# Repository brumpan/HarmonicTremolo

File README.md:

# HarmonicTremolo
A harmonic tremolo effect board for audio

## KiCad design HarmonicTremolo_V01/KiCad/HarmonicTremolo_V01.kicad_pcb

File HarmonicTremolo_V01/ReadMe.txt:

// This project may be replicated by hobbiest and DIY enthusiasts only. The schematics, circuit, and PCB files are not to be used for profit by any commercial, private or third-party entity. \\

Author: Brendan Dickerson
Date: May 2022
Revision: 01
Title: Harmonic Tremolo
Description: Frequency dependent tremolo effect for audio.

This is an audio effect board that can easily be placed into any enclosure or compounded into an existing effects enclosure.

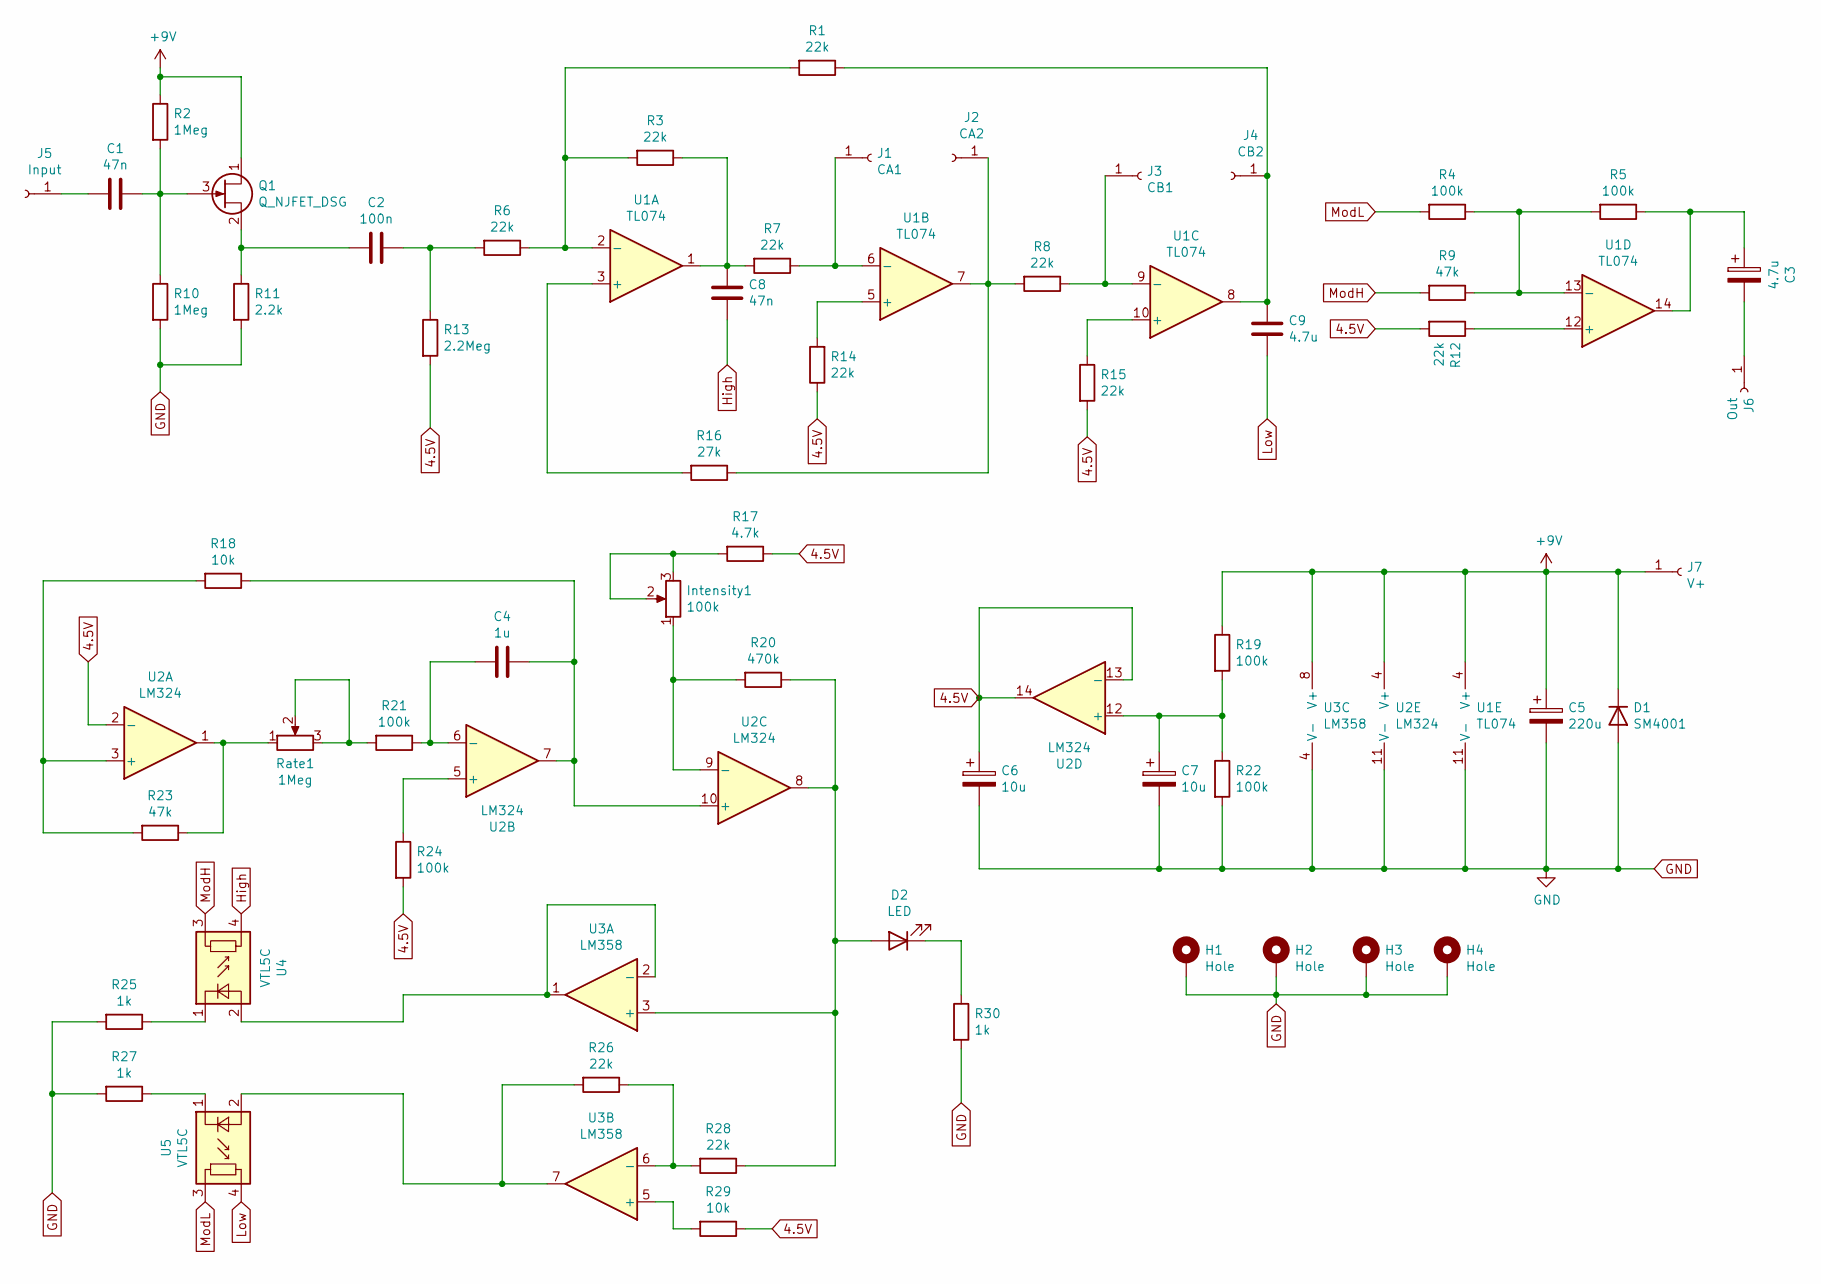
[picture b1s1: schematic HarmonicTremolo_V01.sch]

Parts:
C1, C8: 47n; C_Rect_L7.0mm_W2.5mm_P5.00mm
C2: 100n; C_Rect_L7.0mm_W2.5mm_P5.00mm
C3, C9: 4.7u; CP_Radial_D5.0mm_P2.00mm
C4: 1u; C_Rect_L7.0mm_W3.5mm_P5.00mm
C5: 220u; CP_Radial_D6.3mm_P2.50mm
C6, C7: 10u; CP_Radial_D5.0mm_P2.00mm
D1: SM4001; D_SOD-123
D2: LED; LED_D5.0mm
H1, H2, H3, H4: Hole; MountingHole_3mm_Pad_TopBottom
Intensity1: 100k; SolderWire-1sqmm_1x03_P7.8mm_D1.4mm_OD3.9mm
J1: CA1; SolderWire-0.75sqmm_1x01_D1.25mm_OD3.5mm
J2: CA2; SolderWire-0.75sqmm_1x01_D1.25mm_OD3.5mm
J3: CB1; SolderWire-0.75sqmm_1x01_D1.25mm_OD3.5mm
J4: CB2; SolderWire-0.75sqmm_1x01_D1.25mm_OD3.5mm
J5: Input; SolderWire-0.75sqmm_1x01_D1.25mm_OD3.5mm
J6: Out; SolderWire-0.75sqmm_1x01_D1.25mm_OD3.5mm
J7: V+; SolderWire-0.75sqmm_1x01_D1.25mm_OD3.5mm
Q1: Q_NJFET_DSG; TO-92_Inline_Wide
R1, R3, R6, R7, R8, R12, R14, R15: 22k; R_Axial_DIN0207_L6.3mm_D2.5mm_P10.16mm_Horizontal
R2, R10: 1Meg; R_Axial_DIN0207_L6.3mm_D2.5mm_P10.16mm_Horizontal
R4, R5: 100k; R_Axial_DIN0207_L6.3mm_D2.5mm_P10.16mm_Horizontal
R9: 47k; R_Axial_DIN0207_L6.3mm_D2.5mm_P10.16mm_Horizontal
R11: 2.2k; R_Axial_DIN0207_L6.3mm_D2.5mm_P10.16mm_Horizontal
R13: 2.2Meg; R_Axial_DIN0207_L6.3mm_D2.5mm_P10.16mm_Horizontal
R16: 27k; R_Axial_DIN0207_L6.3mm_D2.5mm_P10.16mm_Horizontal
R17: 4.7k; R_1206_3216Metric_Pad1.30x1.75mm_HandSolder
R18, R29: 10k; R_1206_3216Metric_Pad1.30x1.75mm_HandSolder
R19, R21, R22, R24: 100k; R_1206_3216Metric_Pad1.30x1.75mm_HandSolder
R20: 470k; R_1206_3216Metric_Pad1.30x1.75mm_HandSolder
R23: 47k; R_1206_3216Metric_Pad1.30x1.75mm_HandSolder
R25, R27, R30: 1k; R_1206_3216Metric_Pad1.30x1.75mm_HandSolder
R26, R28: 22k; R_1206_3216Metric_Pad1.30x1.75mm_HandSolder
Rate1: 1Meg; SolderWire-1sqmm_1x03_P7.8mm_D1.4mm_OD3.9mm
U1: TL074; DIP-14_W7.62mm_Socket
U2: LM324; SOIC-14_3.9x8.7mm_P1.27mm
U3: LM358; SOIC-8_3.9x4.9mm_P1.27mm
U4, U5: VTL5C; Vactrol

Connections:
4.5V: C6.1, R12.2, R13.2, R14.1, R15.2, R17.1, R24.2, R29.1, U2.2 (-), U2.13 (-), U2.14
+9V: C5.1, D1.1 (K), J7.1, Q1.1 (D), R2.1, R19.1, U1.4 (V+), U2.4 (V+), U3.8 (V+)
GND: C5.2, C6.2, C7.2, D1.2 (A), H1.1, H2.1, H3.1, H4.1, R10.2, R11.2, R22.2, R25.2, R27.2, R30.2, U1.11 (V-), U2.11 (V-), U3.4 (V-)
High: C8.2, U4.4
Low: C9.2, U5.4
ModH: R9.2, U4.3
ModL: R4.2, U5.3
unnamed: C1.1, Q1.3 (G), R2.2, R10.1
unnamed: C1.2, J5.1
unnamed: C2.1, R6.2, R13.1
unnamed: C2.2, Q1.2 (S), R11.1
unnamed: C3.1, R5.1, U1.14
unnamed: C3.2, J6.1
unnamed: C4.1, R18.1, U2.7, U2.10 (+)
unnamed: C4.2, R21.1, U2.6 (-)
unnamed: C7.1, R19.2, R22.1, U2.12 (+)
unnamed: C8.1, R3.1, R7.2, U1.1
unnamed: C9.1, J4.1, R1.1, U1.8
unnamed: D2.1 (K), R30.1
unnamed: D2.2 (A), R20.1, R28.1, U2.8, U3.3 (+)
unnamed: Intensity1.1, R20.2, U2.9 (-)
unnamed: Intensity1.2, Intensity1.3, R17.2
unnamed: J1.1, R7.1, U1.6 (-)
unnamed: J2.1, R8.2, R16.1, U1.7
unnamed: J3.1, R8.1, U1.9 (-)
unnamed: R1.2, R3.2, R6.1, U1.2 (-)
unnamed: R4.1, R5.2, R9.1, U1.13 (-)
unnamed: R12.1, U1.12 (+)
unnamed: R14.2, U1.5 (+)
unnamed: R15.1, U1.10 (+)
unnamed: R16.2, U1.3 (+)
unnamed: R18.2, R23.2, U2.3 (+)
unnamed: R21.2, Rate1.2, Rate1.3
unnamed: R23.1, Rate1.1, U2.1
unnamed: R24.1, U2.5 (+)
unnamed: R25.1, U4.1 (-)
unnamed: R26.1, R28.2, U3.6 (-)
unnamed: R26.2, U3.7, U5.2 (+)
unnamed: R27.1, U5.1 (-)
unnamed: R29.2, U3.5 (+)
unnamed: U3.1, U3.2 (-), U4.2 (+)

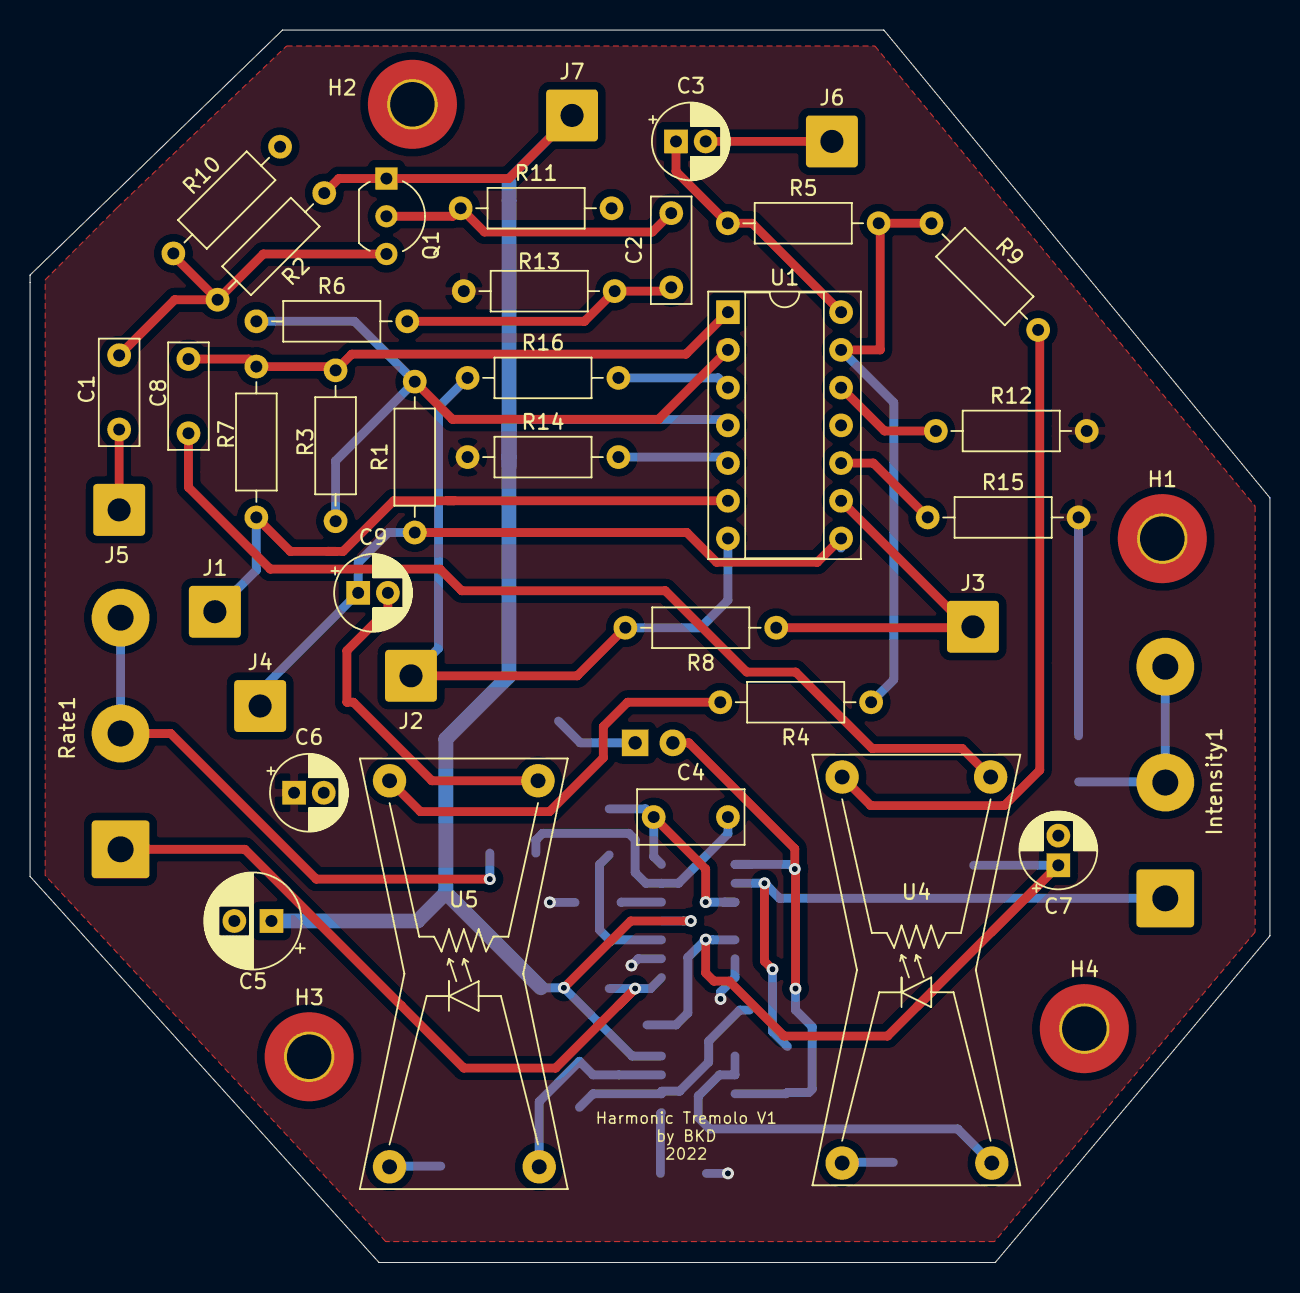
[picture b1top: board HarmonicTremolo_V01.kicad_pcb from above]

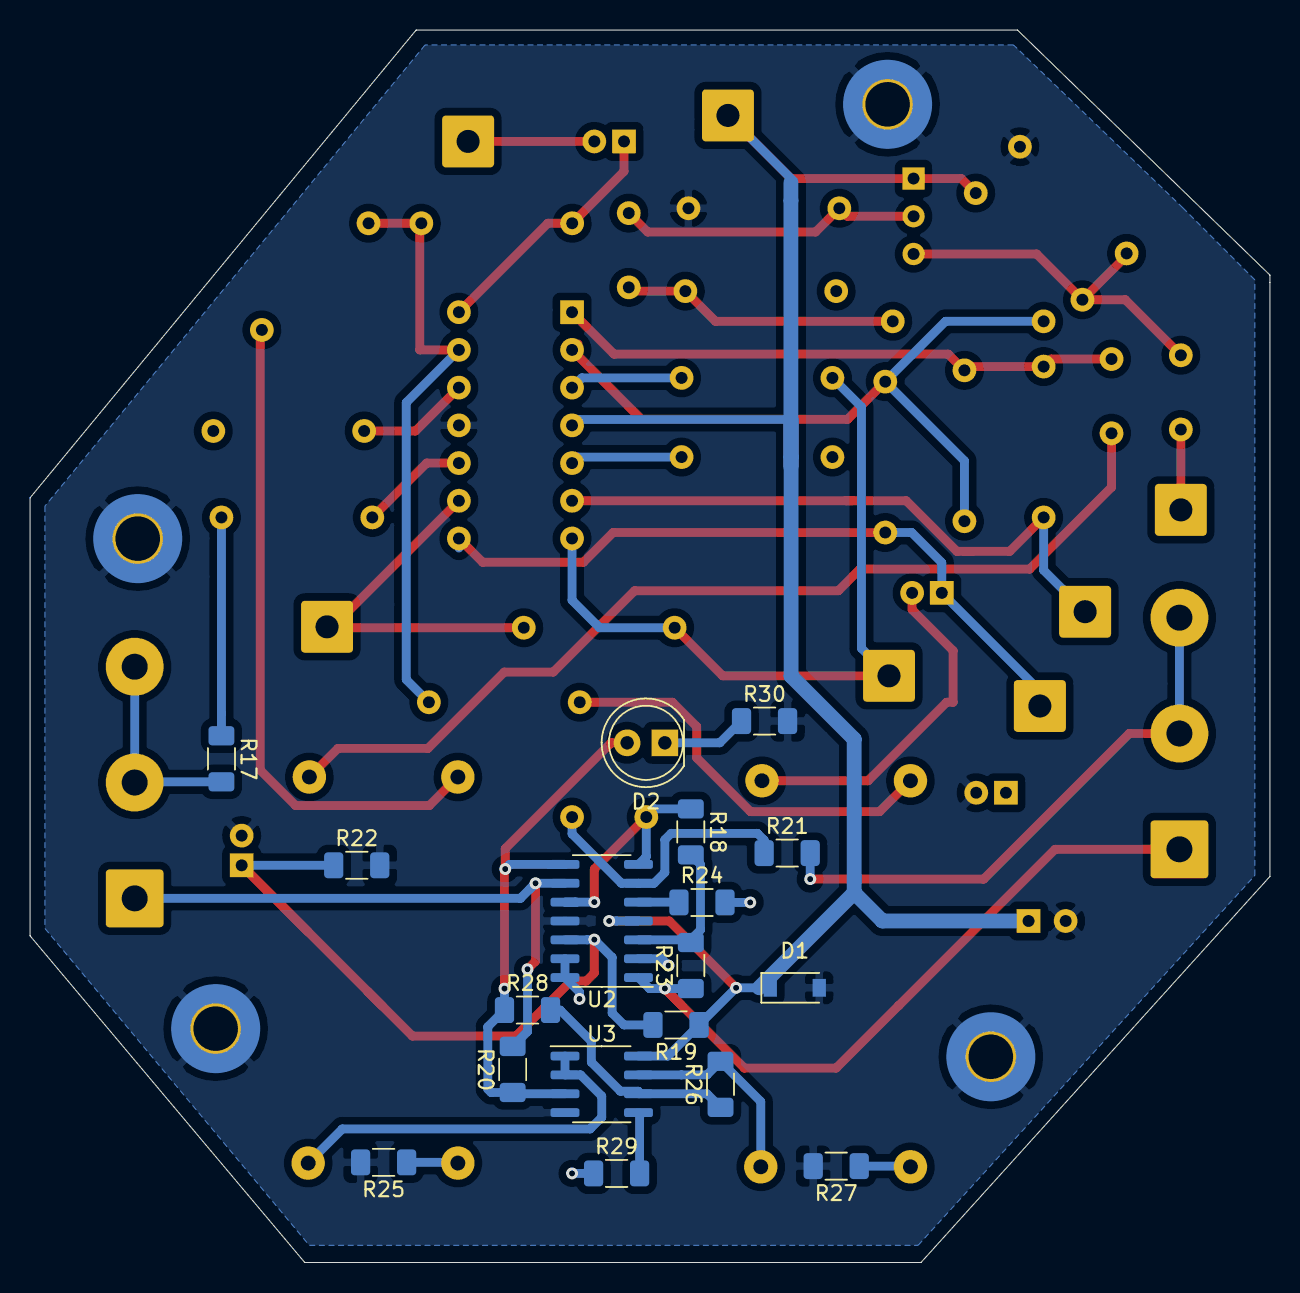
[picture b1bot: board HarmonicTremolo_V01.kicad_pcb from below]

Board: 2 copper layers, 83.5 x 83.0 mm, 60 parts (18 on the bottom side), 41 nets.
